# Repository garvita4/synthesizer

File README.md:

# Synthesizer

<!-- Final CAD Images -->

A portable, standalone digital synthesizer and musical workstation featuring a 30-key hot-swap mechanical keyboard (26 musical piano keys and 4 customizable performance pads), 5x EC11 rotary encoders, and a vibrant TFT display. Powered by the ESP32-S3-WROOM-1-N16R8 microcontroller and backed by a massive 10,000mAh LiPo battery with a dedicated physical ON/OFF slide switch and IP5306 wake/activation button, ChronosSynth delivers studio-grade 32-bit I2S DAC audio through dual stereo speakers or an auto-switching 3.5mm headphone jack, complete with per-key addressable RGB illumination, MicroSD sample storage, and native USB Type-C connectivity.

## Features & Hardware Design

[Full Schematic](Images/schematics.png)

### 30-Key Matrix & Backlighting
Features a 30-key tactile mechanical deck (26 staggered piano keys and a 2x2 customizable control pad cluster) arranged in a 5-row by 6-column diode-protected matrix (`1N4148W`)[cite: 13, 14]. Utilizes Kailh MX hot-swap sockets for solderless switch swapping. Paired with 35x RGB LEDs (`SK6812MINI-E`) for per-key and status glow.

### Audio Engine & Output
High-fidelity digital audio synthesis is handled via an onboard `PCM5102A` 32-bit I2S DAC with passive RC low-pass output filtering. Audio is routed through a `PJ-307` 5-pin auto-switching 3.5mm stereo headphone jack that automatically mutes the onboard `PAM8403D` (3W x 2 Class-D) stereo speaker amplifier when headphones are plugged.

### Connectivity & Storage
A dual USB Type-C architecture separates high-current battery charging from native USB data, firmware flashing, and USB Type-C communication. An onboard SMD push-pull MicroSD card slot is wired over a dedicated high-speed SPI bus, saving custom synth patches, and recording MIDI sequences.

### Power & Battery
Powered by a high-capacity **10,000mAh 3.7V LiPo battery**  controlled via a master **Power ON/OFF slide switch**. Integrated battery management (`IP5306`) provides safe USB-C charging, a dedicated tactile push button (`KEY`) to activate/wake the charging and boost IC, and a regulated `+5V` output rail for the Class-D audio amplifier and RGB LED chain. An `AP2112K-3.3` LDO voltage regulator steps `+5V` down to a clean, low-noise `+3.3V` rail for the digital logic, screen, and DAC.

### Microcontroller (ESP32-S3)
The `ESP32-S3-WROOM-1-N16R8` (16MB Flash, 8MB Octal PSRAM) serves as the brain of the workstation, handling real-time polyphonic audio synthesis, direct GPIO key matrix scanning, DMA-driven SPI display rendering, and USB-MIDI output.

### Rotary Encoders & I2C Port Expander
Five `EC11` rotary encoders with integrated push switches provide real-time tactile control over synthesis parameters . All 15 encoder signals are routed through an `MCP23017-E/SO` 16-bit I2C port expander and hardware interrupt to keep main MCU pins free for the switch matrix and dual SPI buses.

### Display Interface
Integrated color TFT display (3.5" / 1.9" `ST7789` IPS SPI interface) driven over a dedicated hardware SPI bus for live waveform visualization, instrument selection, envelope graphs, and battery status 

---

## PCB Layout & Specifications
The hardware is built on a custom **2-layer FR4 PCB** measuring approximately **300mm x 100mm**. Both Top and Bottom layers feature continuous **Ground (`GND`) copper pours** to shield high-speed SPI/I2S digital lines and keep the analog audio path free of switching noise.

---

## CAD & 3D-Printed Enclosure
To fit on standard desktop 3D printer beds despite its 300mm+ width, the enclosure is split into **4 modular interlocking sections**:
* **Top Left Faceplate**
* **Top Right Faceplate**
* **Bottom Left Shell**
* **Bottom Right Shell**

### Enclosure Assembly Instructions

1. **Bottom Shell Assembly (Bottom Left + Bottom Right):**
   The bottom tray is split into left and right halves featuring a precision mechanical alignment interlock. The **Bottom Left** half features circular alignment grooves (**10mm diameter, 2.5mm depth**), while the **Bottom Right** half features matching extruded alignment bosses/rods (**10mm diameter, 2.5mm height**). Apply (super glue) to the mating faces, press the alignment rods firmly into the grooves so the bottom tray sits completely flush, and allow it to cure.

2. **Top Faceplate Assembly (Top Left + Top Right):**
   The top control faceplate halves use the exact same **10mm diameter x 2.5mm** groove-and-rod interlocking alignment system. Apply super glue to the inner seam, align the cylindrical pins into their mating recesses, and clamp until bonded.

## Firmware
The current is prototype and not tested it will be tested and updated in future and then the hardware will me manufactured. Full end-to-end testing, feature integration, and fine-tuning will be completed once hardware production and assembly are finalized.

## Bill of Materials (BOM)

| Part | Description | Qty | Unit Price (USD) | Total Price (USD) | Vendor |
| :--- | :--- | :---: | :---: | :---: | :--- |
| **Espressif ESP32-S3-WROOM-1-N16R8** | MCU Module | 1 | $4.73 | $4.73 | Robu.in |
| **MCP23017-E/SO** | 16-Bit I2C GPIO Expander | 1 | $2.44 | $2.44 | LCSC India |
| **PCM5102A** | 32-Bit I2S Digital-to-Analog Converter (DAC) | 1 | $4.38 | $4.38 | LCSC India |
| **PAM8403** | Class-D Stereo Audio Amplifier | 1 | $1.97 | $1.97 | LCSC India |
| **IP5306** | Power Bank / LiPo Charger & 5V Boost IC | 1 | $2.39 | $2.39 | LCSC |
| **AMS1117-3.3** | 3.3V LDO Voltage Regulator | 1 | $0.83 | $0.83 | LCSC India |
| **SJ1-3525NG-GR** | 3.5mm Stereo Audio Jack with Internal Switch | 1 | $1.22 | $1.22 | LionCircuits |
| **Mechanical Key Switches** | Tactile/Linear Switches (Packs of 10) | 5 | $2.11 | $10.55 | Meckeys |
| **EC11 Rotary Encoder** | Sound / Parameter Control Knobs | 5 | $0.61 | $3.05 | Robu.in |
| **SMD Power Inductor (2.2uH)** | Shielded Power Inductor | 1 | $1.17 | $1.17 | LCSC India |
| **Kailh MX Hot-Swap Sockets** | Hot-Swap Switch Sockets (Packs of 10) | 4 | $0.84 | $3.36 | Meckeys |
| **SK6812MINI-E** | Addressable RGB LEDs (Packs of 10) | 4 | $0.56 | $2.24 | LCSC India |
| **SMD Resistors** | Passive Resistors (Assorted Values) | 40 | $0.01 | $0.40 | Ktron |
| **SMD Capacitors** | Passive Capacitors (Assorted Values) | 30 | $0.01 | $0.30 | Ktron |
| **3.7V LiPo Battery** | Rechargeable Battery Pack | 1 | $4.20 | $4.20 | MakerBazar |
| **Total** | | | | **$43.23** | |

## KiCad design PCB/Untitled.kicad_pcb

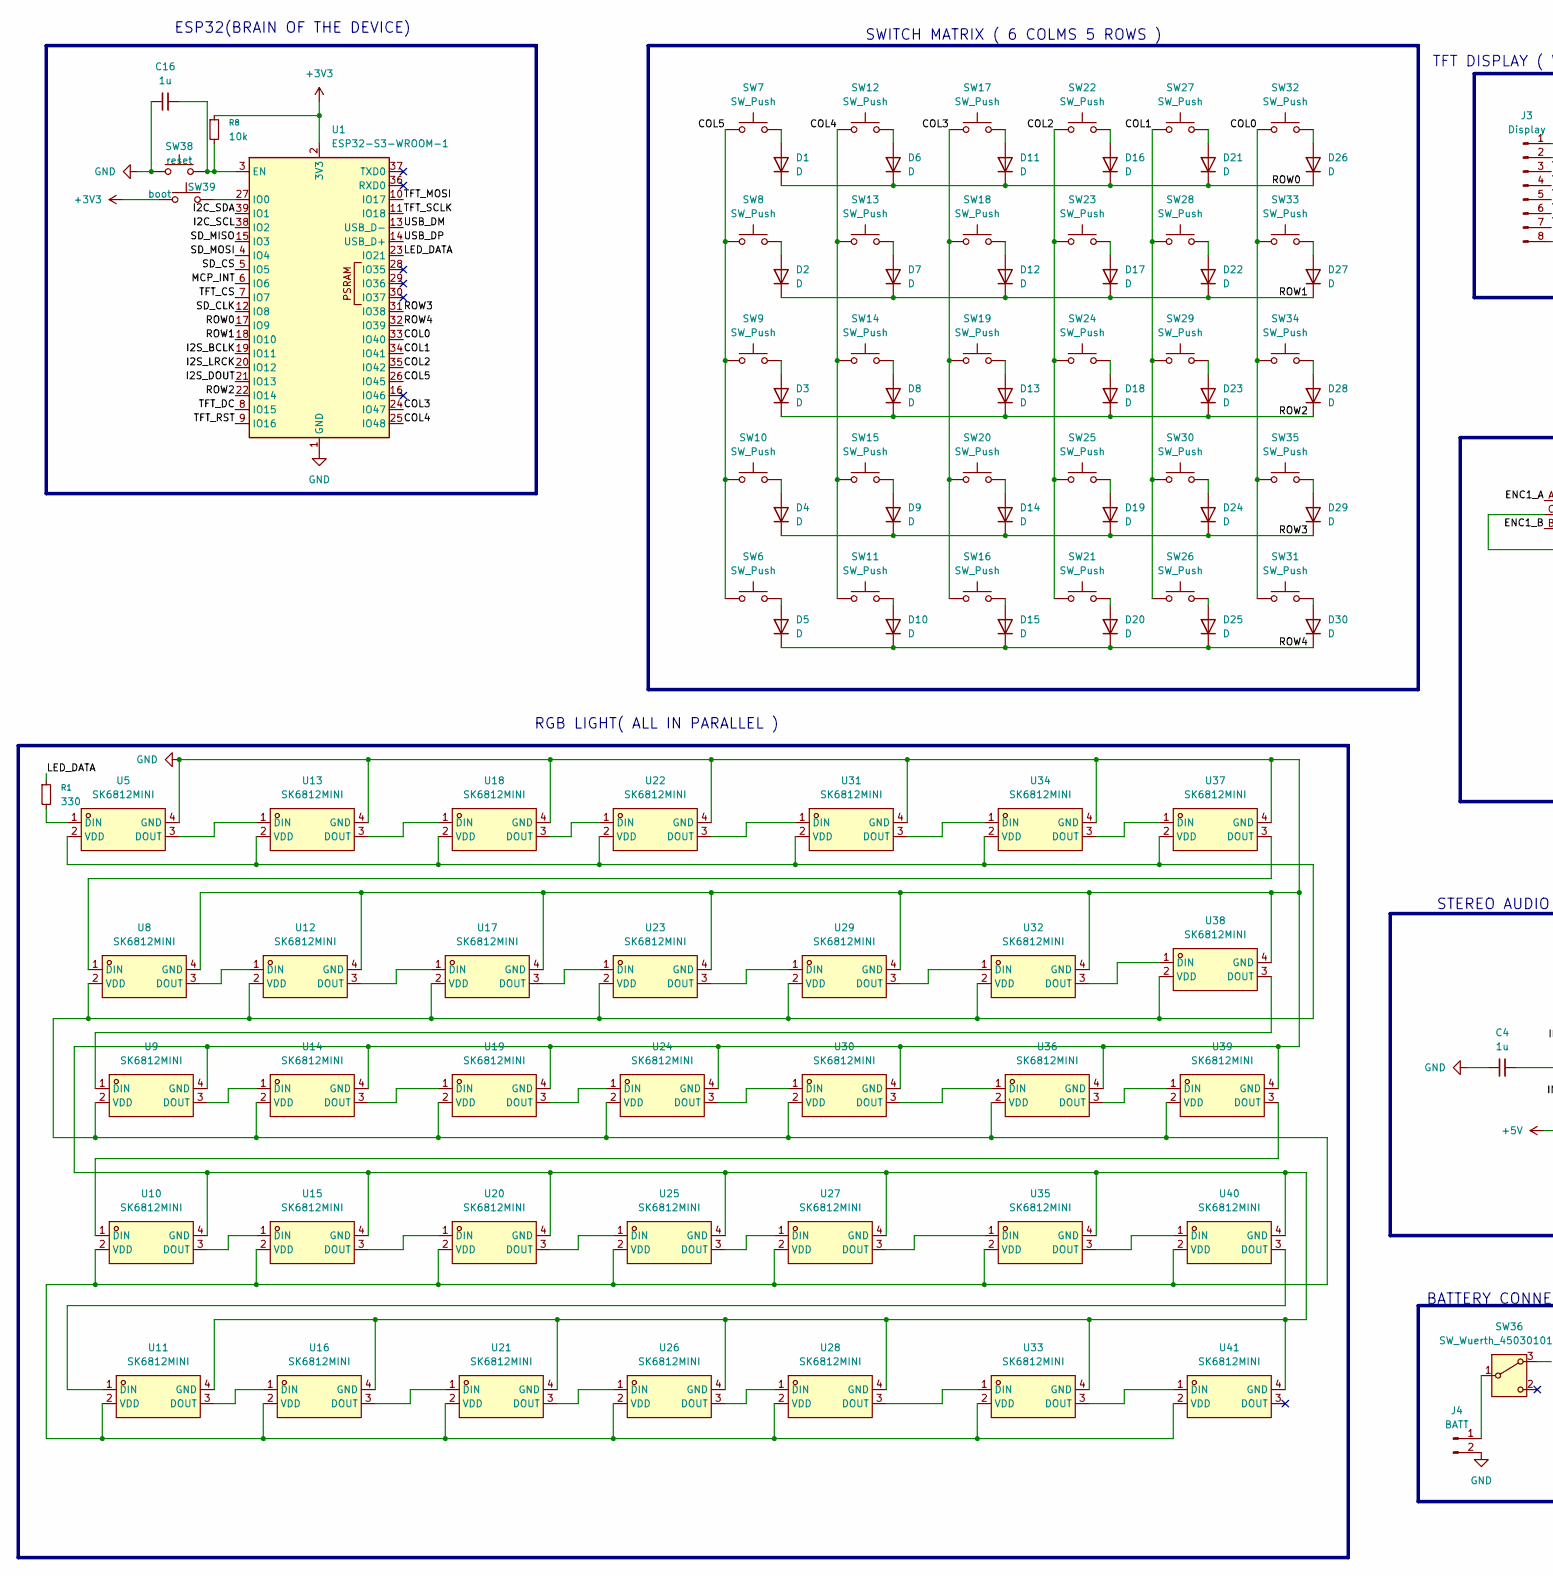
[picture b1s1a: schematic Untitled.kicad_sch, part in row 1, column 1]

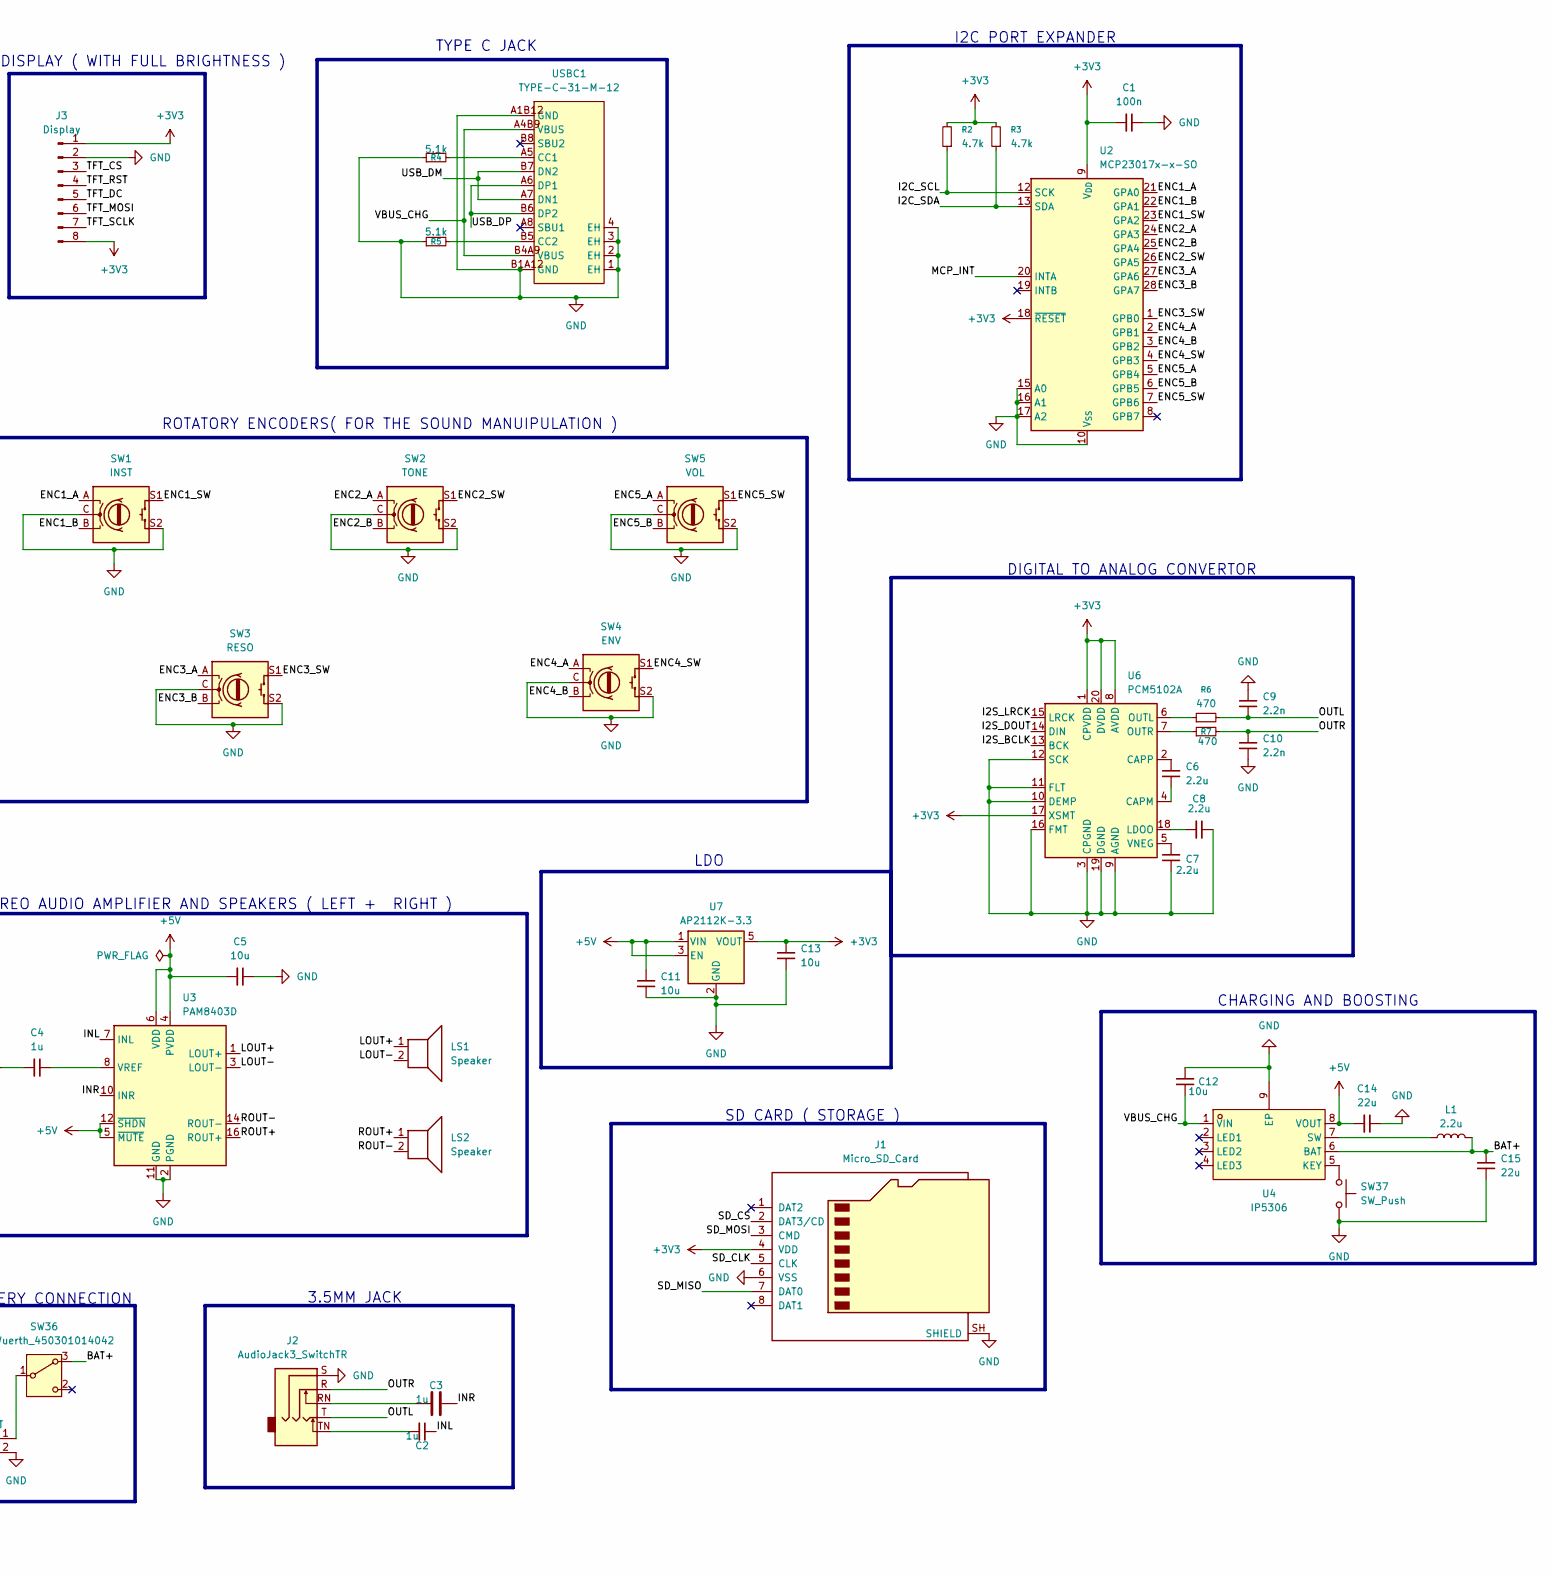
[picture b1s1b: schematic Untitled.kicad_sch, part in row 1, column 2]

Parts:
C1: 100n; C_0805_2012Metric
C2, C3, C4, C16: 1u; C_0805_2012Metric
C5, C11, C12, C13: 10u; C_0805_2012Metric
C6, C7, C8: 2.2u; C_0805_2012Metric
C9, C10: 2.2n; C_0805_2012Metric
C14, C15: 22u; C_0805_2012Metric
D1, D2, D3, D4, D5, D6, D7, D8, D9, D10, D11, D12, D13, D14, D15, D16, D17, D18, D19, D20, D21, D22, D23, D24, D25, D26, D27, D28, D29, D30: D; D_SOD-123
J1: Micro_SD_Card; microSD_HC_Hirose_DM3AT-SF-PEJM5
J2: AudioJack3_SwitchTR; Jack_3.5mm_CUI_SJ1-3525N_Horizontal
J3: Display; PinHeader_1x09_P2.00mm_Vertical
J4: BATT; PinHeader_1x02_P1.27mm_Vertical
L1: 2.2u; L_Bourns-SRN4018
LS1, LS2: Speaker; PinHeader_1x02_P1.00mm_Vertical
R1: 330; R_0805_2012Metric
R2, R3: 4.7k; R_0805_2012Metric
R4, R5: 5.1k; R_0805_2012Metric
R6, R7: 470; R_0805_2012Metric
R8: 10k; R_0805_2012Metric
SW1: INST; RotaryEncoder_Alps_EC11E-Switch_Vertical_H20mm
SW2: TONE; RotaryEncoder_Alps_EC11E-Switch_Vertical_H20mm
SW3: RESO; RotaryEncoder_Alps_EC11E-Switch_Vertical_H20mm
SW4: ENV; RotaryEncoder_Alps_EC11E-Switch_Vertical_H20mm
SW5: VOL; RotaryEncoder_Alps_EC11E-Switch_Vertical_H20mm
SW6, SW7, SW8, SW9, SW10, SW11, SW12, SW13, SW14, SW15, SW16, SW17, SW18, SW19, SW20, SW21, SW22, SW23, SW24, SW25, SW26, SW27, SW28, SW29, SW30, SW31, SW32, SW33, SW34, SW35, SW37: SW_Push; SW_Hotswap_Kailh_MX_1.00u
SW36: SW_Wuerth_450301014042; SW_Slide-03_Wuerth-WS-SLTV_10x2.5x6.4_P2.54mm
SW38: reset; SW_SPST_B3U-1000P
SW39: boot; SW_SPST_B3U-1000P
U1: ESP32-S3-WROOM-1
U2: MCP23017x-x-SO; SOIC-28W_7.5x17.9mm_P1.27mm
U3: PAM8403D; SOIC-16_3.9x9.9mm_P1.27mm
U4: IP5306; ESOP-8_L4.9-W3.9-P1.27-LS6.0-BL-EP; MPN IP5306; LCSC Part C181692
U5, U8, U9, U10, U11, U12, U13, U14, U15, U16, U17, U18, U19, U20, U21, U22, U23, U24, U25, U26, U27, U28, U29, U30, U31, U32, U33, U34, U35, U36, U37, U38, U39, U40, U41: SK6812MINI; LED_SK6812MINI-E_3.2x2.8mm_P1.5mm_ReverseMount; MPN SK6812mini-012; LCSC Part C2886570
U6: PCM5102A; TSSOP-20_4.4x6.5mm_P0.65mm
U7: AP2112K-3.3; SOT-23-5
USBC1: TYPE-C-31-M-12; USB-C_SMD-TYPE-C-31-M-12_1; MPN TYPE-C-31-M-12; LCSC Part C165948

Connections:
+3V3: C1.1, C13.1, J1.4 (VDD), J3.1, J3.8, R2.2, R3.2, R8.1, SW39.1, U1.2 (3V3), U2.9 (V_{DD}), U2.18 (~RESET), U6.1 (CPVDD), U6.8 (AVDD), U6.17 (XSMT), U6.20 (DVDD), U7.5 (VOUT)
+5V: C5.1, C11.1, C14.1, U3.4 (PVDD), U3.5 (~MUTE), U3.6 (VDD), U3.12 (~SHDN), U3.13 (PVDD), U4.8 (VOUT), U7.1 (VIN), U7.3 (EN)
/BAT+: C15.1, L1.2, SW36.3 (A), U4.6 (BAT)
/COL0: SW31.1, SW32.1, SW33.1, SW34.1, SW35.1, U1.33 (IO40)
/COL1: SW26.1, SW27.1, SW28.1, SW29.1, SW30.1, U1.34 (IO41)
/COL2: SW21.1, SW22.1, SW23.1, SW24.1, SW25.1, U1.35 (IO42)
/COL3: SW16.1, SW17.1, SW18.1, SW19.1, SW20.1, U1.24 (IO47)
/COL4: SW11.1, SW12.1, SW13.1, SW14.1, SW15.1, U1.25 (IO48)
/COL5: SW6.1, SW7.1, SW8.1, SW9.1, SW10.1, U1.26 (IO45)
/ENC1_A: SW1.A, U2.21 (GPA0)
/ENC1_B: SW1.B, U2.22 (GPA1)
/ENC1_SW: SW1.S1, U2.23 (GPA2)
/ENC2_A: SW2.A, U2.24 (GPA3)
/ENC2_B: SW2.B, U2.25 (GPA4)
/ENC2_SW: SW2.S1, U2.26 (GPA5)
/ENC3_A: SW3.A, U2.27 (GPA6)
/ENC3_B: SW3.B, U2.28 (GPA7)
/ENC3_SW: SW3.S1, U2.1 (GPB0)
/ENC4_A: SW4.A, U2.2 (GPB1)
/ENC4_B: SW4.B, U2.3 (GPB2)
/ENC4_SW: SW4.S1, U2.4 (GPB3)
/ENC5_A: SW5.A, U2.5 (GPB4)
/ENC5_B: SW5.B, U2.6 (GPB5)
/ENC5_SW: SW5.S1, U2.7 (GPB6)
/I2C_SCL: R2.1, U1.38 (IO2), U2.12 (SCK)
/I2C_SDA: R3.1, U1.39 (IO1), U2.13 (SDA)
/I2S_BCLK: U1.19 (IO11), U6.13 (BCK)
/I2S_DOUT: U1.21 (IO13), U6.14 (DIN)
/I2S_LRCK: U1.20 (IO12), U6.15 (LRCK)
/INL: C2.1, U3.7 (INL)
/INR: C3.2, U3.10 (INR)
/LED_DATA: R1.1, U1.23 (IO21)
/LOUT+: LS1.1, U3.1 (LOUT+)
/LOUT-: LS1.2, U3.3 (LOUT-)
/MCP_INT: U1.6 (IO6), U2.20 (INTA)
/OUTL: C9.2, J2.T, R6.2
/OUTR: C10.1, J2.R, R7.2
/ROUT+: LS2.1, U3.16 (ROUT+)
/ROUT-: LS2.2, U3.14 (ROUT-)
/ROW0: D1.1 (K), D6.1 (K), D11.1 (K), D16.1 (K), D21.1 (K), D26.1 (K), U1.17 (IO9)
/ROW1: D2.1 (K), D7.1 (K), D12.1 (K), D17.1 (K), D22.1 (K), D27.1 (K), U1.18 (IO10)
/ROW2: D3.1 (K), D8.1 (K), D13.1 (K), D18.1 (K), D23.1 (K), D28.1 (K), U1.22 (IO14)
/ROW3: D4.1 (K), D9.1 (K), D14.1 (K), D19.1 (K), D24.1 (K), D29.1 (K), U1.31 (IO38)
/ROW4: D5.1 (K), D10.1 (K), D15.1 (K), D20.1 (K), D25.1 (K), D30.1 (K), U1.32 (IO39)
/SD_CLK: J1.5 (CLK), U1.12 (IO8)
/SD_CS: J1.2 (DAT3/CD), U1.5 (IO5)
/SD_MISO: J1.7 (DAT0), U1.15 (IO3)
/SD_MOSI: J1.3 (CMD), U1.4 (IO4)
/TFT_CS: J3.3, U1.7 (IO7)
/TFT_DC: J3.5, U1.8 (IO15)
/TFT_MOSI: J3.6, U1.10 (IO17)
/TFT_RST: J3.4, U1.9 (IO16)
/TFT_SCLK: J3.7, U1.11 (IO18)
/USB_DM: U1.13 (USB_D-), USBC1.A7 (DN1), USBC1.B7 (DN2)
/USB_DP: U1.14 (USB_D+), USBC1.A6 (DP1), USBC1.B6 (DP2)
/VBUS_CHG: C12.2, U4.1 (VIN), USBC1.A4B9 (VBUS), USBC1.B4A9 (VBUS)
GND: C1.2, C4.1, C5.2, C7.2, C8.2, C9.1, C10.2, C11.2, C12.1, C13.2, C14.2, C15.2, C16.2, J1.6 (VSS), J1.SH (SHIELD), J2.S, J3.2, J4.2, R4.1, R5.1, SW1.C, SW1.S2, SW2.C, SW2.S2, SW3.C, SW3.S2, SW4.C, SW4.S2, SW5.C, SW5.S2, SW37.2, SW38.1, U1.1 (GND), U1.40 (GND), U1.41 (GND), U2.10 (V_{SS}), U2.15 (A0), U2.16 (A1), U2.17 (A2), U3.2 (PGND), U3.11 (GND), U3.15 (PGND), U4.9 (EP), U5.4 (GND), U6.3 (CPGND), U6.9 (AGND), U6.10 (DEMP), U6.11 (FLT), U6.12 (SCK), U6.16 (FMT), U6.19 (DGND), U7.2 (GND), U8.4 (GND), U9.4 (GND), U10.4 (GND), U11.4 (GND), U12.4 (GND), U13.4 (GND), U14.4 (GND), U15.4 (GND), U16.4 (GND), U17.4 (GND), U18.4 (GND), U19.4 (GND), U20.4 (GND), U21.4 (GND), U22.4 (GND), U23.4 (GND), U24.4 (GND), U25.4 (GND), U26.4 (GND), U27.4 (GND), U28.4 (GND), U29.4 (GND), U30.4 (GND), U31.4 (GND), U32.4 (GND), U33.4 (GND), U34.4 (GND), U35.4 (GND), U36.4 (GND), U37.4 (GND), U38.4 (GND), U39.4 (GND), U40.4 (GND), U41.4 (GND), USBC1.1 (EH), USBC1.2 (EH), USBC1.3 (EH), USBC1.4 (EH), USBC1.A1B12 (GND), USBC1.B1A12 (GND)
unnamed: C2.2, J2.TN
unnamed: C3.1, J2.RN
unnamed: D1.2 (A), SW7.2
unnamed: D2.2 (A), SW8.2
unnamed: D3.2 (A), SW9.2
unnamed: D4.2 (A), SW10.2
unnamed: D5.2 (A), SW6.2
unnamed: D6.2 (A), SW12.2
unnamed: D7.2 (A), SW13.2
unnamed: D8.2 (A), SW14.2
unnamed: D9.2 (A), SW15.2
unnamed: D10.2 (A), SW11.2
unnamed: D11.2 (A), SW17.2
unnamed: D12.2 (A), SW18.2
unnamed: D13.2 (A), SW19.2
unnamed: D14.2 (A), SW20.2
unnamed: D15.2 (A), SW16.2
unnamed: D16.2 (A), SW22.2
unnamed: D17.2 (A), SW23.2
unnamed: D18.2 (A), SW24.2
unnamed: D19.2 (A), SW25.2
unnamed: D20.2 (A), SW21.2
unnamed: D21.2 (A), SW27.2
unnamed: D22.2 (A), SW28.2
unnamed: D23.2 (A), SW29.2
unnamed: D24.2 (A), SW30.2
unnamed: D25.2 (A), SW26.2
unnamed: D26.2 (A), SW32.2
unnamed: D27.2 (A), SW33.2
unnamed: D28.2 (A), SW34.2
unnamed: D29.2 (A), SW35.2
unnamed: D30.2 (A), SW31.2
unnamed: J4.1, SW36.1 (B)
unnamed: C16.1, R8.2, SW38.2, U1.3 (EN)
unnamed: SW39.2, U1.27 (IO0)
unnamed: C4.2, U3.8 (VREF)
unnamed: SW37.1, U4.5 (KEY)
unnamed: L1.1, U4.7 (SW)
unnamed: R1.2, U5.1 (DIN)
unnamed: C6.2, U6.4 (CAPM)
unnamed: C6.1, U6.2 (CAPP)
unnamed: C8.1, U6.18 (LDOO)
unnamed: R6.1, U6.6 (OUTL)
unnamed: R7.1, U6.7 (OUTR)
unnamed: C7.1, U6.5 (VNEG)
unnamed: U10.1 (DIN), U39.3 (DOUT)
unnamed: U10.3 (DOUT), U15.1 (DIN)
unnamed: U5.2 (VDD), U8.2 (VDD), U9.2 (VDD), U10.2 (VDD), U11.2 (VDD), U12.2 (VDD), U13.2 (VDD), U14.2 (VDD), U15.2 (VDD), U16.2 (VDD), U17.2 (VDD), U18.2 (VDD), U19.2 (VDD), U20.2 (VDD), U21.2 (VDD), U22.2 (VDD), U23.2 (VDD), U24.2 (VDD), U25.2 (VDD), U26.2 (VDD), U27.2 (VDD), U28.2 (VDD), U29.2 (VDD), U30.2 (VDD), U31.2 (VDD), U32.2 (VDD), U33.2 (VDD), U34.2 (VDD), U35.2 (VDD), U36.2 (VDD), U37.2 (VDD), U38.2 (VDD), U39.2 (VDD), U40.2 (VDD), U41.2 (VDD)
unnamed: U11.1 (DIN), U40.3 (DOUT)
unnamed: U11.3 (DOUT), U16.1 (DIN)
unnamed: U8.3 (DOUT), U12.1 (DIN)
unnamed: U12.3 (DOUT), U17.1 (DIN)
unnamed: U5.3 (DOUT), U13.1 (DIN)
unnamed: U13.3 (DOUT), U18.1 (DIN)
unnamed: U9.3 (DOUT), U14.1 (DIN)
unnamed: U14.3 (DOUT), U19.1 (DIN)
unnamed: U15.3 (DOUT), U20.1 (DIN)
unnamed: U16.3 (DOUT), U21.1 (DIN)
unnamed: U17.3 (DOUT), U23.1 (DIN)
unnamed: U18.3 (DOUT), U22.1 (DIN)
unnamed: U19.3 (DOUT), U24.1 (DIN)
unnamed: U20.3 (DOUT), U25.1 (DIN)
unnamed: U21.3 (DOUT), U26.1 (DIN)
unnamed: U22.3 (DOUT), U31.1 (DIN)
unnamed: U23.3 (DOUT), U29.1 (DIN)
unnamed: U24.3 (DOUT), U30.1 (DIN)
unnamed: U25.3 (DOUT), U27.1 (DIN)
unnamed: U26.3 (DOUT), U28.1 (DIN)
unnamed: U27.3 (DOUT), U35.1 (DIN)
unnamed: U28.3 (DOUT), U33.1 (DIN)
unnamed: U29.3 (DOUT), U32.1 (DIN)
unnamed: U30.3 (DOUT), U36.1 (DIN)
unnamed: U31.3 (DOUT), U34.1 (DIN)
unnamed: U32.3 (DOUT), U38.1 (DIN)
unnamed: U33.3 (DOUT), U41.1 (DIN)
unnamed: U34.3 (DOUT), U37.1 (DIN)
unnamed: U35.3 (DOUT), U40.1 (DIN)
unnamed: U36.3 (DOUT), U39.1 (DIN)
unnamed: U8.1 (DIN), U37.3 (DOUT)
unnamed: U9.1 (DIN), U38.3 (DOUT)
unnamed: R4.2, USBC1.A5 (CC1)
unnamed: R5.2, USBC1.B5 (CC2)

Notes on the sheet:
TYPE C JACK
3.5MM JACK
CHARGING AND BOOSTING
DIGITAL TO ANALOG CONVERTOR
TFT DISPLAY ( WITH FULL BRIGHTNESS )
STEREO AUDIO AMPLIFIER AND SPEAKERS ( LEFT + RIGHT )
I2C PORT EXPANDER
RGB LIGHT( ALL IN PARALLEL )
ROTATORY ENCODERS( FOR THE SOUND MANUIPULATION )
SD CARD ( STORAGE )
SWITCH MATRIX ( 6 COLMS 5 ROWS )
LDO
BATTERY CONNECTION
ESP32(BRAIN OF THE DEVICE)

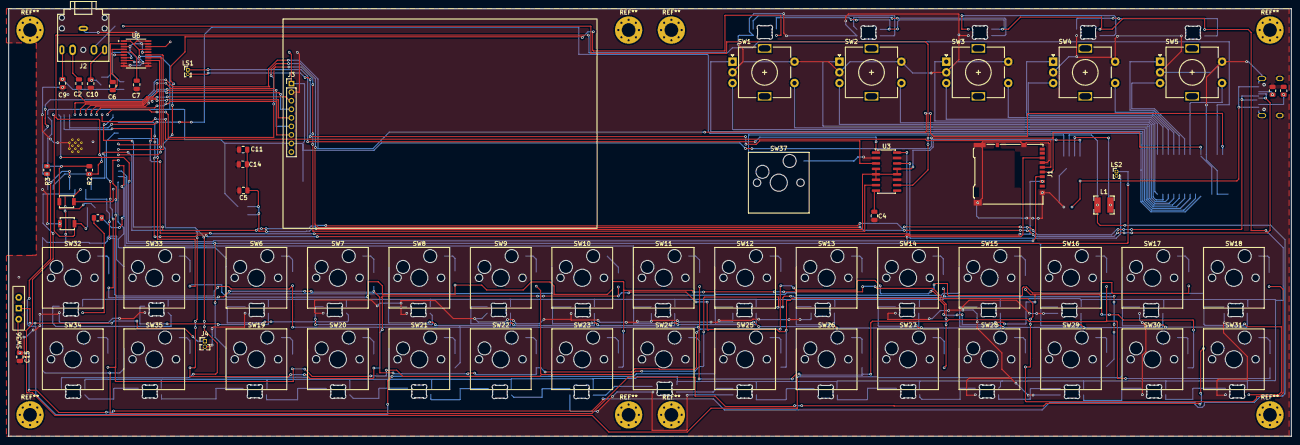
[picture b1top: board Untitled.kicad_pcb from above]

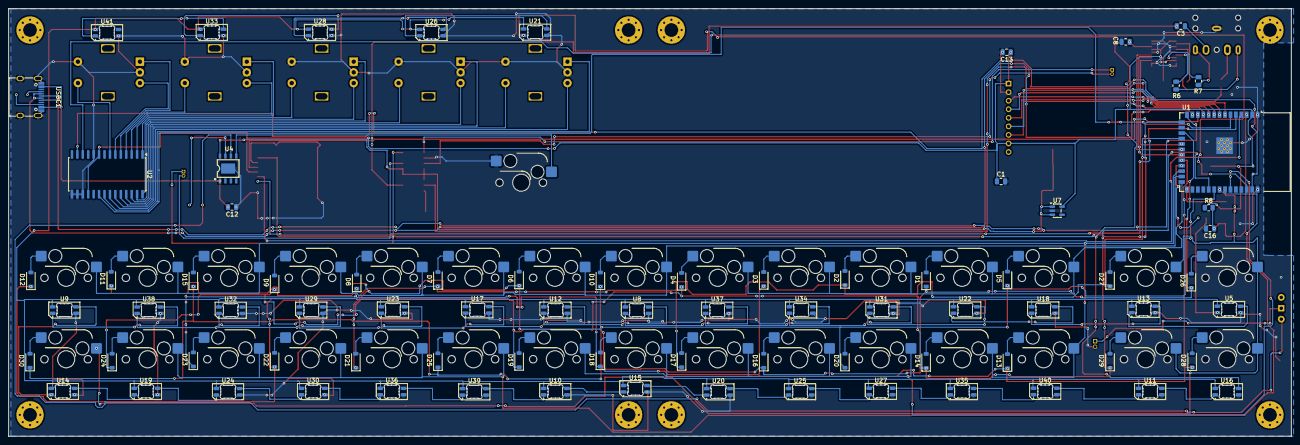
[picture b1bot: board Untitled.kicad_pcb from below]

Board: 2 copper layers, 300.0 x 100.0 mm, 142 parts (79 on the bottom side), 139 nets.

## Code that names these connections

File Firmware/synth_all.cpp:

// Merged firmware
#include <Arduino.h>
#include <stdarg.h>
#include <math.h>
#include <Wire.h>
#include <Adafruit_NeoPixel.h>
#include <LovyanGFX.hpp>
#include <FS.h>
#include <SD.h>
#include <SPI.h>
#include <USB.h>
#include <USBMIDI.h>

#include <driver/i2s.h>
#include <esp_heap_caps.h>

// board
#pragma once
// ===== Hardware map =====
#include <Arduino.h>

// ---- Audio (PCM5102A, I2S) ----
#define AUDIO_SR     44100
#define AUDIO_BLOCK  128
#define MAX_VOICES   16
constexpr int PIN_I2S_BCLK = 11, PIN_I2S_LRCK = 12, PIN_I2S_DOUT = 13;

// ---- I2C / MCP23017 ----
constexpr int PIN_I2C_SDA = 1, PIN_I2C_SCL = 2, PIN_MCP_INT = 6;
constexpr uint8_t MCP_ADDR = 0x20;
#define ENC_STEPS_PER_DETENT 4
#define ENC_INVERT           0
constexpr uint8_t ENCODER_DIR_INVERT_MASK = 0b00000;

// ---- microSD ----
constexpr int PIN_SD_MISO = 3, PIN_SD_MOSI = 4, PIN_SD_CS = 5, PIN_SD_SCLK = 8;

// ---- ST7789 ----
constexpr int PIN_TFT_CS = 7, PIN_TFT_DC = 15, PIN_TFT_RST = 16, PIN_TFT_MOSI = 17, PIN_TFT_SCLK = 18;
constexpr int TFT_WIDTH = 320;
constexpr int TFT_HEIGHT = 170;
constexpr int TFT_COL_OFFSET = 0;
constexpr int TFT_ROW_OFFSET = 35;
constexpr uint8_t TFT_ROTATION = 1;

// ---- SK6812 ----
constexpr int PIN_LED_DATA = 21;
#define LED_COUNT 35
#define LED_MAX_BRIGHTNESS 90

constexpr uint8_t kMacroPadLedIndex[4] = {0, 1, 2, 3};
constexpr uint8_t kNoteKeyLedIndex[26]  = {4,5,6,7,8,9,10,11,12,13,14,15,16,17,18,19,20,21,22,23,24,25,26,27,28,29};
constexpr uint8_t kEncoderLedIndex[5]  = {30, 31, 32, 33, 34};

constexpr int NUM_ROWS = 5, NUM_COLS = 6, NUM_KEYS = 30, NUM_NOTE_KEYS = 26;
constexpr uint8_t ROW_PINS[NUM_ROWS] = {9, 10, 14, 38, 39};
constexpr uint8_t COL_PINS[NUM_COLS] = {40, 41, 42, 47, 48, 45};
#define MATRIX_SETTLE_US 10
#define KEY_DEBOUNCE_SCANS 3

enum MacroPadKey : uint8_t {
  PAD_MODE = 26,
  PAD_HOLD = 27,
  PAD_OCT_DOWN = 28,
  PAD_OCT_UP_SHIFT = 29
};
constexpr int KEY_MODE = PAD_MODE;
constexpr int KEY_LATCH = PAD_HOLD;
constexpr int KEY_OCTDN = PAD_OCT_DOWN;
constexpr int KEY_OCTUP = PAD_OCT_UP_SHIFT;
extern const uint8_t kMatrixMap[NUM_ROWS][NUM_COLS];
inline int keyId(int row, int col) {
  if (row < 0 || row >= NUM_ROWS || col < 0 || col >= NUM_COLS) return 255;
  return kMatrixMap[row][col];
}

// types
enum : uint8_t { FAM_SYNTH = 0, FAM_GUITAR = 1, FAM_SAMPLER = 2, FAM_COUNT = 3 };
enum : uint8_t { MODE_POLY = 0, MODE_MONO = 1, MODE_ARP = 2, MODE_COUNT = 3 };
enum : uint8_t { W_SINE = 0, W_TRI, W_SAW, W_SQUARE, W_COUNT };

struct Patch {
  char    name[12];
  uint8_t family, wave1, wave2;
  int8_t  semi2;
  float   detune;
  float   mix;
  float   cutoff, reso, envAmt;
  float   a, d, s, r;
  float   fx;
};

struct Sample { int16_t* data; uint32_t len; uint32_t rate; uint8_t root; char name[12]; };

struct SynthState {
  Patch   patch;
  float   master;
  uint8_t fxType;
  uint8_t mode;
  float   bpm;
  int8_t  octave;
  bool    latch;
  int     sampleIdx;
};
extern SynthState g_state;

struct UiState {
  uint8_t family = 0;
  int16_t patchIdx[3] = {0, 0, 0};
  uint8_t presetSlot = 0;
  uint8_t envSel = 0;
  bool    fxVol = false;
  bool    shift = false, shiftUsed = false;
};
extern UiState g_ui;

#define PRESET_MAGIC 0x31534E53u
struct PresetFile {
  uint32_t magic; uint16_t version, size;
  Patch patch; float master; float bpm; uint8_t fxType, mode; int32_t sampleIdx;
};

enum : uint8_t { EV_KEY_DOWN, EV_KEY_UP, EV_ENC_TURN, EV_ENC_DOWN, EV_ENC_UP };
struct InputEvent { uint8_t type; uint8_t id; int8_t val; };

// patches
static const Patch kSynth[] = {
  {"SawLead",  FAM_SYNTH, W_SAW,    W_SAW,     0,  8.f, .5f, .65f, .20f, .30f, .005f, .30f, .70f, .25f, .15f},
  {"SubBass",  FAM_SYNTH, W_SAW,    W_SQUARE, -12, 4.f, .6f, .35f, .25f, .50f, .002f, .20f, .50f, .10f, .00f},
  {"WarmPad",  FAM_SYNTH, W_SAW,    W_SAW,     0, 14.f, .5f, .45f, .10f, .15f, .600f, .80f, .80f, 1.2f, .35f},
  {"PluckSyn", FAM_SYNTH, W_SAW,    W_TRI,     0,  6.f, .4f, .30f, .30f, .70f, .001f, .25f, .00f, .20f, .20f},
  {"E-Piano",  FAM_SYNTH, W_SINE,   W_TRI,    12,  3.f, .3f, .70f, .00f, .10f, .002f, 1.2f, .20f, .50f, .20f},
  {"PwrSquare",FAM_SYNTH, W_SQUARE, W_SQUARE,  0,  7.f, .5f, .60f, .15f, .25f, .003f, .20f, .80f, .20f, .10f},
  {"Organ",    FAM_SYNTH, W_SINE,   W_SINE,   12,  0.f, .5f, 1.0f, .00f, .00f, .005f, .05f, 1.0f, .06f, .10f},
  {"Brass",    FAM_SYNTH, W_SAW,    W_SAW,     0,  5.f, .5f, .40f, .15f, .50f, .080f, .20f, .70f, .15f, .10f},
};
static const Patch kGuitar[] = {
  {"Nylon", FAM_GUITAR, 0,0,0, 0,0, .45f, 0,0, .001f, 3.0f, 1.f, .12f, .20f},
  {"Steel", FAM_GUITAR, 0,0,0, 0,0, .80f, 0,0, .001f, 4.0f, 1.f, .15f, .20f},
  {"Muted", FAM_GUITAR, 0,0,0, 0,0, .25f, 0,0, .001f, 0.8f, 1.f, .08f, .10f},
};
static const Patch kSamplerBase = {"Sample", FAM_SAMPLER, 0,0,0, 0,0, 1.0f, 0,0, .001f, .10f, 1.f, .15f, .15f};
